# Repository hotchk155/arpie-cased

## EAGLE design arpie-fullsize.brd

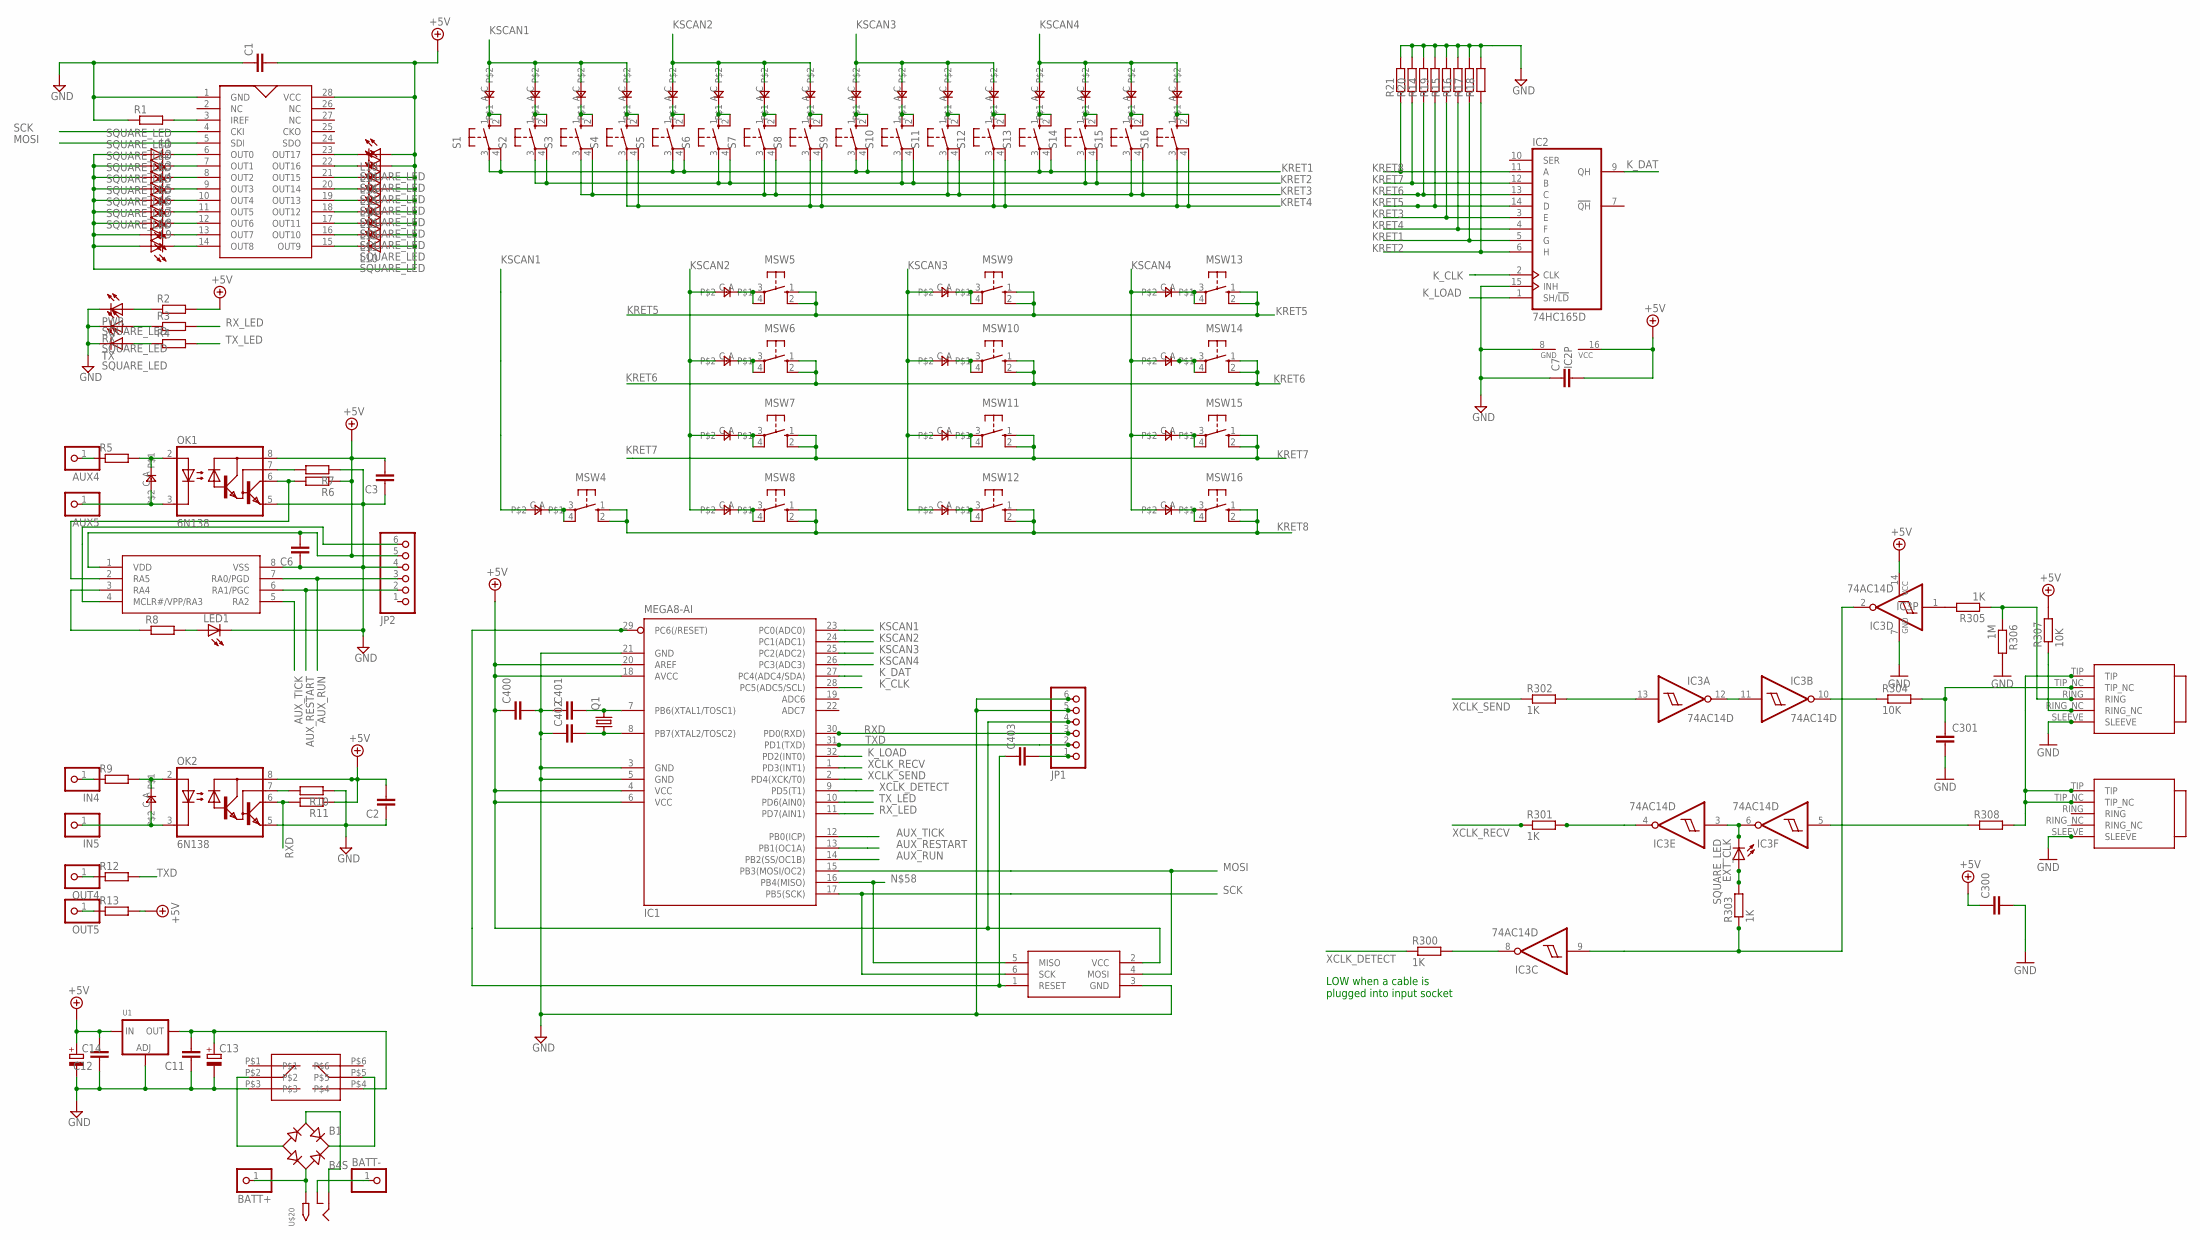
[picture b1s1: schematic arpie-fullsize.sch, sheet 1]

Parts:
AUX4, AUX5: PINHD-1X1; 1X01
B1: B4S; MBS
BATT+: PINHD-1X1; 1X01
BATT-: PINHD-1X1; 1X01
C1, C2, C3, C6, C7, C11, C12, C300, C301, C400, C401, C402, C403: C-EUC0805; C0805
C13, C14: CPOL-EUE2-5; E2-5
EXT_CLK: SQUARE_LED; RECT_LED
IC1: MEGA8-AI; TQFP32-08
IC2: 74HC165D; SO16
IC3: 74AC14D; SO14
IN4, IN5: PINHD-1X1; 1X01
JP1, JP2: PINHD-1X6; 1X06
L1, L2, L3, L4, L5, L6, L7, L8, L9, L10, L11, L12, L13, L14, L15, L16, L17, L18: SQUARE_LED; RECT_LED
LED1: LEDCHIP-LED0805; CHIP-LED0805
MSW4, MSW5, MSW6, MSW7, MSW8, MSW9, MSW10, MSW11, MSW12, MSW13, MSW14, MSW15, MSW16: 40-XX; B3F-40XX
OK1, OK2: 6N138; DIL08
OUT4, OUT5: PINHD-1X1; 1X01
PWR: SQUARE_LED; RECT_LED
Q1: CRYSTALHC49U-V; HC49U-V
R1, R2, R3, R4, R5, R6, R7, R8, R9, R10, R11, R12, R13, R14, R15, R16, R17, R18, R19, R20, R21, R308: R-EU_R0805; R0805
R300, R301, R302, R303, R305: 1K; R0805
R304, R307: 10K; R0805
R306: 1M; R0805
RX: SQUARE_LED; RECT_LED
S1, S2, S3, S4, S5, S6, S7, S8, S9, S10, S11, S12, S13, S14, S15, S16: 10-XX; B3F-10XX
TX: SQUARE_LED; RECT_LED
U1: LM1117SOT223-REFLOW; SOT223-R
U$1: WS2803; SO28W
U$2, U$3, U$4, U$5, U$6, U$7, U$8, U$9, U$10, U$11, U$12, U$13, U$14, U$15, U$16, U$17, U$21, U$22, U$23, U$24, U$25, U$26, U$27, U$28, U$29, U$30, U$31, U$32, U$33, U$36, U$37: 0805DIODE
U$18, U$19: TRUCONNECTJACK
U$20: 2.1MMJACKTHM; PJ-102A
U$34: TAG_CONN_AVR; TC2030-MCP-NL
U$35: PIC12F1822SO08; SO08
U$38: 2P2T_LATCHING

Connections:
+5V: C1.2, C2.2, C3.2, C6.2, C7.2, C12.2, C14.+, C300.1, C400.1, IC1.4 (VCC), IC1.6 (VCC), IC1.18 (AVCC), IC1.20 (AREF), IC2.16 (VCC), IC3.14 (VCC), JP1.4, JP2.5, L1.AN (A), L2.AN (A), L3.AN (A), L4.AN (A), L5.AN (A), L6.AN (A), L7.AN (A), L8.AN (A), L9.AN (A), L10.AN (A), L11.AN (A), L12.AN (A), L13.AN (A), L14.AN (A), L15.AN (A), L16.AN (A), L17.AN (A), L18.AN (A), OK1.8 (VCC), OK2.8 (VCC), R2.2, R6.1, R11.1, R13.2, R307.2, U1.3 (IN), U$1.28 (VCC), U$34.2 (VCC), U$35.1 (VDD)
AUX_RESTART: IC1.13 (PB1(OC1A)), JP2.2, U$35.6 (RA1/PGC)
AUX_RUN: IC1.14 (PB2(SS/OC1B)), JP2.3, U$35.7 (RA0/PGD)
AUX_TICK: IC1.12 (PB0(ICP)), U$35.5 (RA2)
GND: C1.1, C2.1, C3.1, C6.1, C7.1, C11.1, C12.1, C13.-, C14.-, C300.2, C301.2, C400.2, C401.1, C402.1, IC1.3 (GND), IC1.5 (GND), IC1.21 (GND), IC2.8 (GND), IC2.15 (INH), IC3.7 (GND), JP1.5, JP1.6, JP2.4, LED1.C, OK1.5 (GND), OK2.5 (GND), PWR.CA (C), R1.1, R7.1, R10.1, R14.2, R15.2, R16.2, R17.2, R18.2, R19.2, R20.2, R21.2, R306.2, RX.CA (C), TX.CA (C), U1.1 (ADJ), U$1.1 (GND), U$18.SLEEVE, U$19.SLEEVE, U$34.3 (GND), U$35.8 (VSS), U$38.P$3
KRET1: IC2.5 (G), R17.1, S1.3, S1.4 (P1), S5.3, S5.4 (P1), S9.3, S9.4 (P1), S13.3, S13.4 (P1)
KRET2: IC2.6 (H), R18.1, S2.3, S2.4 (P1), S6.3, S6.4 (P1), S10.3, S10.4 (P1), S14.3, S14.4 (P1)
KRET3: IC2.3 (E), R15.1, S3.3, S3.4 (P1), S7.3, S7.4 (P1), S11.3, S11.4 (P1), S15.3, S15.4 (P1)
KRET4: IC2.4 (F), R16.1, S4.3, S4.4 (P1), S8.3, S8.4 (P1), S12.3, S12.4 (P1), S16.3, S16.4 (P1)
KRET5: IC2.14 (D), MSW5.1 (S), MSW5.2 (S1), MSW9.1 (S), MSW9.2 (S1), MSW13.1 (S), MSW13.2 (S1), R19.1
KRET6: IC2.13 (C), MSW6.1 (S), MSW6.2 (S1), MSW10.1 (S), MSW10.2 (S1), MSW14.1 (S), MSW14.2 (S1), R14.1
KRET7: IC2.12 (B), MSW7.1 (S), MSW7.2 (S1), MSW11.1 (S), MSW11.2 (S1), MSW15.1 (S), MSW15.2 (S1), R20.1
KRET8: IC2.11 (A), MSW4.1 (S), MSW4.2 (S1), MSW8.1 (S), MSW8.2 (S1), MSW12.1 (S), MSW12.2 (S1), MSW16.1 (S), MSW16.2 (S1), R21.1
KSCAN1: IC1.23 (PC0(ADC0)), U$2.C, U$3.C, U$4.C, U$5.C, U$21.C
KSCAN2: IC1.24 (PC1(ADC1)), U$6.C, U$7.C, U$8.C, U$9.C, U$22.C, U$23.C, U$24.C, U$25.C
KSCAN3: IC1.25 (PC2(ADC2)), U$10.C, U$11.C, U$12.C, U$13.C, U$26.C, U$27.C, U$28.C, U$29.C
KSCAN4: IC1.26 (PC3(ADC3)), U$14.C, U$15.C, U$16.C, U$17.C, U$30.C, U$31.C, U$32.C, U$33.C
K_CLK: IC1.28 (PC5(ADC5/SCL)), IC2.2 (CLK)
K_DAT: IC1.27 (PC4(ADC4/SDA)), IC2.9 (QH)
K_LOAD: IC1.32 (PD2(INT0)), IC2.1 (SH/!LD)
MOSI: IC1.15 (PB3(MOSI/OC2)), U$1.5 (SDI), U$34.4 (MOSI)
unnamed: L1.CA (C), U$1.6 (OUT0)
unnamed: L2.CA (C), U$1.7 (OUT1)
unnamed: L3.CA (C), U$1.8 (OUT2)
unnamed: L4.CA (C), U$1.9 (OUT3)
unnamed: L5.CA (C), U$1.10 (OUT4)
unnamed: L6.CA (C), U$1.11 (OUT5)
unnamed: L7.CA (C), U$1.12 (OUT6)
unnamed: L8.CA (C), U$1.13 (OUT7)
unnamed: L9.CA (C), U$1.14 (OUT8)
unnamed: L18.CA (C), U$1.23 (OUT17)
unnamed: L17.CA (C), U$1.22 (OUT16)
unnamed: L16.CA (C), U$1.21 (OUT15)
unnamed: L15.CA (C), U$1.20 (OUT14)
unnamed: L14.CA (C), U$1.19 (OUT13)
unnamed: L13.CA (C), U$1.18 (OUT12)
unnamed: L12.CA (C), U$1.17 (OUT11)
unnamed: L11.CA (C), U$1.16 (OUT10)
unnamed: L10.CA (C), U$1.15 (OUT9)
unnamed: S1.1 (S), S1.2 (S1), U$2.A
unnamed: S2.1 (S), S2.2 (S1), U$3.A
unnamed: R1.2, U$1.3 (IREF)
unnamed: S3.1 (S), S3.2 (S1), U$4.A
unnamed: S4.1 (S), S4.2 (S1), U$5.A
unnamed: S5.1 (S), S5.2 (S1), U$6.A
unnamed: S6.1 (S), S6.2 (S1), U$7.A
unnamed: S7.1 (S), S7.2 (S1), U$8.A
unnamed: S8.1 (S), S8.2 (S1), U$9.A
unnamed: S9.1 (S), S9.2 (S1), U$10.A
unnamed: S10.1 (S), S10.2 (S1), U$11.A
unnamed: S11.1 (S), S11.2 (S1), U$12.A
unnamed: S12.1 (S), S12.2 (S1), U$13.A
unnamed: S13.1 (S), S13.2 (S1), U$14.A
unnamed: S14.1 (S), S14.2 (S1), U$15.A
unnamed: S15.1 (S), S15.2 (S1), U$16.A
unnamed: S16.1 (S), S16.2 (S1), U$17.A
unnamed: MSW13.3, MSW13.4 (P1), U$30.A
unnamed: MSW14.3, MSW14.4 (P1), U$31.A
unnamed: MSW16.3, MSW16.4 (P1), U$33.A
unnamed: MSW15.3, MSW15.4 (P1), U$32.A
unnamed: MSW4.3, MSW4.4 (P1), U$21.A
unnamed: MSW5.3, MSW5.4 (P1), U$22.A
unnamed: MSW6.3, MSW6.4 (P1), U$23.A
unnamed: MSW7.3, MSW7.4 (P1), U$24.A
unnamed: MSW8.3, MSW8.4 (P1), U$25.A
unnamed: MSW9.3, MSW9.4 (P1), U$26.A
unnamed: MSW10.3, MSW10.4 (P1), U$27.A
unnamed: MSW11.3, MSW11.4 (P1), U$28.A
unnamed: MSW12.3, MSW12.4 (P1), U$29.A
unnamed: C401.2, IC1.7 (PB6(XTAL1/TOSC1)), Q1.2
unnamed: C402.2, IC1.8 (PB7(XTAL2/TOSC2)), Q1.1
unnamed: PWR.AN (A), R2.1
unnamed: R3.1, RX.AN (A)
unnamed: R4.1, TX.AN (A)
unnamed: OUT4.1, R12.1
unnamed: IC1.16 (PB4(MISO)), U$34.5 (MISO)
unnamed: OUT5.1, R13.1
unnamed: C403.2, JP1.1
unnamed: AUX4.1, R5.1
unnamed: OK1.2 (A), R5.2, U$36.A
unnamed: AUX5.1, OK1.3 (C), U$36.C
unnamed: JP2.6, U$35.4 (MCLR#/VPP/RA3)
unnamed: IN4.1, R9.1
unnamed: OK2.2 (A), R9.2, U$37.A
unnamed: IN5.1, OK2.3 (C), U$37.C
unnamed: OK1.7 (VB), R7.2
unnamed: OK1.6 (VO), R6.2, U$35.2 (RA5)
unnamed: OK2.7 (VB), R10.2
unnamed: R8.1, U$35.3 (RA4)
unnamed: LED1.A, R8.2
unnamed: R308.2, U$18.TIP, U$19.TIP, U$19.TIP_NC
unnamed: C301.1, R304.2, U$18.TIP_NC
unnamed: IC3.10 (O), R304.1
unnamed: IC3.11 (I), IC3.12 (O)
unnamed: IC3.13 (I), R302.2
unnamed: R307.1, U$18.RING_NC
unnamed: R305.1, R306.1, U$18.RING
unnamed: IC3.1 (I), R305.2
unnamed: EXT_CLK.CA (C), IC3.3 (I), IC3.6 (O)
unnamed: IC3.5 (I), R308.1
unnamed: IC3.4 (O), R301.2
unnamed: IC3.2 (O), IC3.9 (I), R303.1
unnamed: EXT_CLK.AN (A), R303.2
unnamed: IC3.8 (O), R300.2
unnamed: BATT-.1, U$20.RING_SW
unnamed: B1.AC2, BATT+.1, U$20.TIP
unnamed: B1.-, U$38.P$2
unnamed: B1.+, U$38.P$5
unnamed: C11.2, C13.+, U1.2 (OUT), U$38.P$4
unnamed: B1.AC1, U$20.RING
RESET: C403.1, IC1.29 (PC6(/RESET)), U$34.1 (RESET)
RXD: IC1.30 (PD0(RXD)), JP1.3, OK2.6 (VO), R11.2
RX_LED: IC1.11 (PD7(AIN1)), R3.2
SCK: IC1.17 (PB5(SCK)), U$1.4 (CKI), U$34.6 (SCK)
TXD: IC1.31 (PD1(TXD)), JP1.2, R12.2
TX_LED: IC1.10 (PD6(AIN0)), R4.2
XCLK_DETECT: IC1.9 (PD5(T1)), R300.1
XCLK_RECV: IC1.1 (PD3(INT1)), R301.1
XCLK_SEND: IC1.2 (PD4(XCK/T0)), R302.1

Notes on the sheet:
LOW when a cable is plugged into input socket

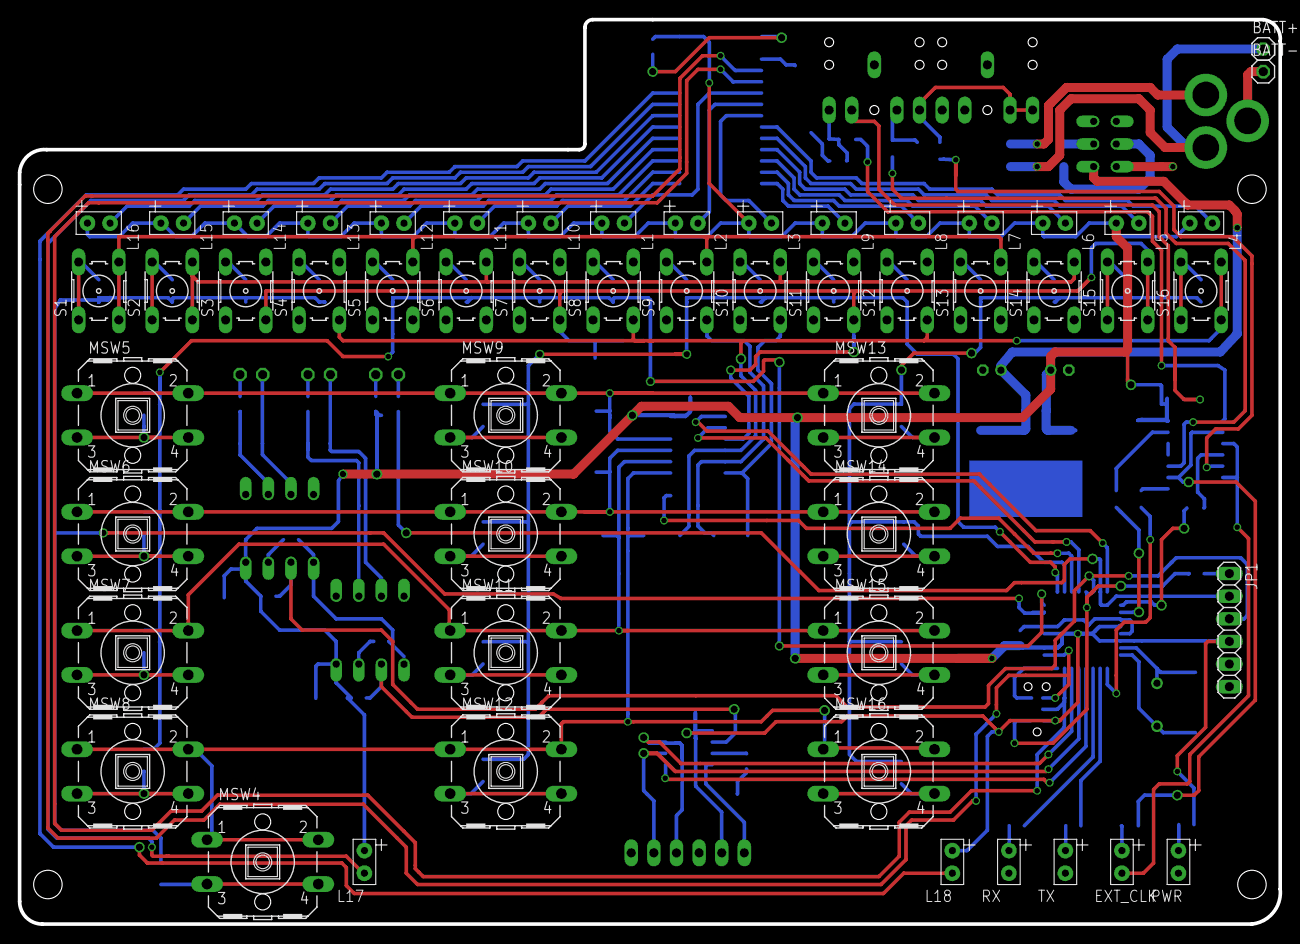
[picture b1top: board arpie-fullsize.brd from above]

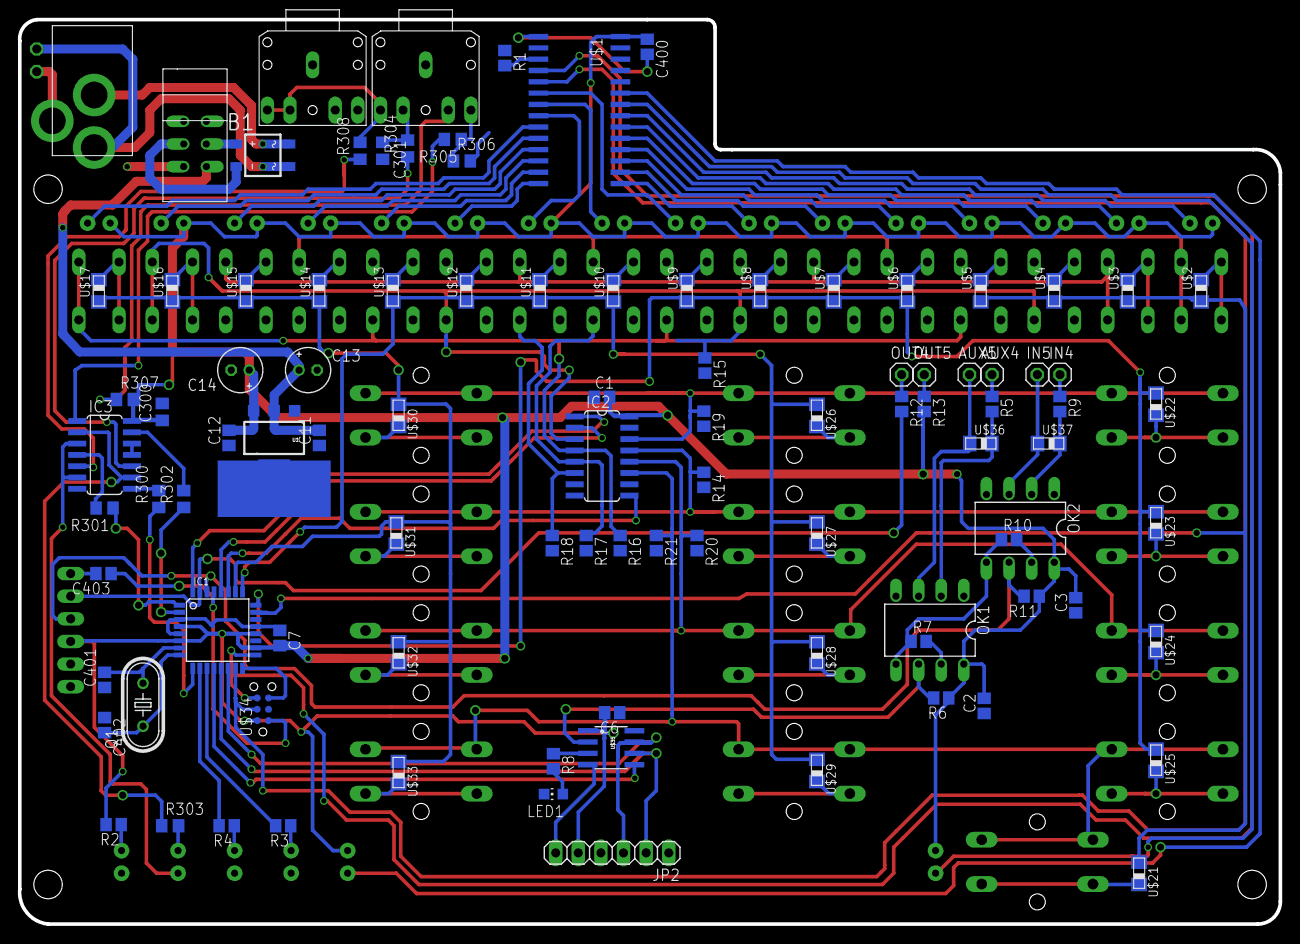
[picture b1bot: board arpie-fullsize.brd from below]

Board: 2 copper layers, 141.6 x 101.6 mm, 153 parts (99 on the bottom side), 119 nets.

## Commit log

2015-02-07 :lollipop: Added .gitattributes
2015-02-07 first cut
2015-02-07 first cut again

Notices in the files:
parts and their libraries:
jasons_stuff: ©2009 ROFA.cz - modified and updated by Robert Darlington ‹rdarlington@gmail.com›
